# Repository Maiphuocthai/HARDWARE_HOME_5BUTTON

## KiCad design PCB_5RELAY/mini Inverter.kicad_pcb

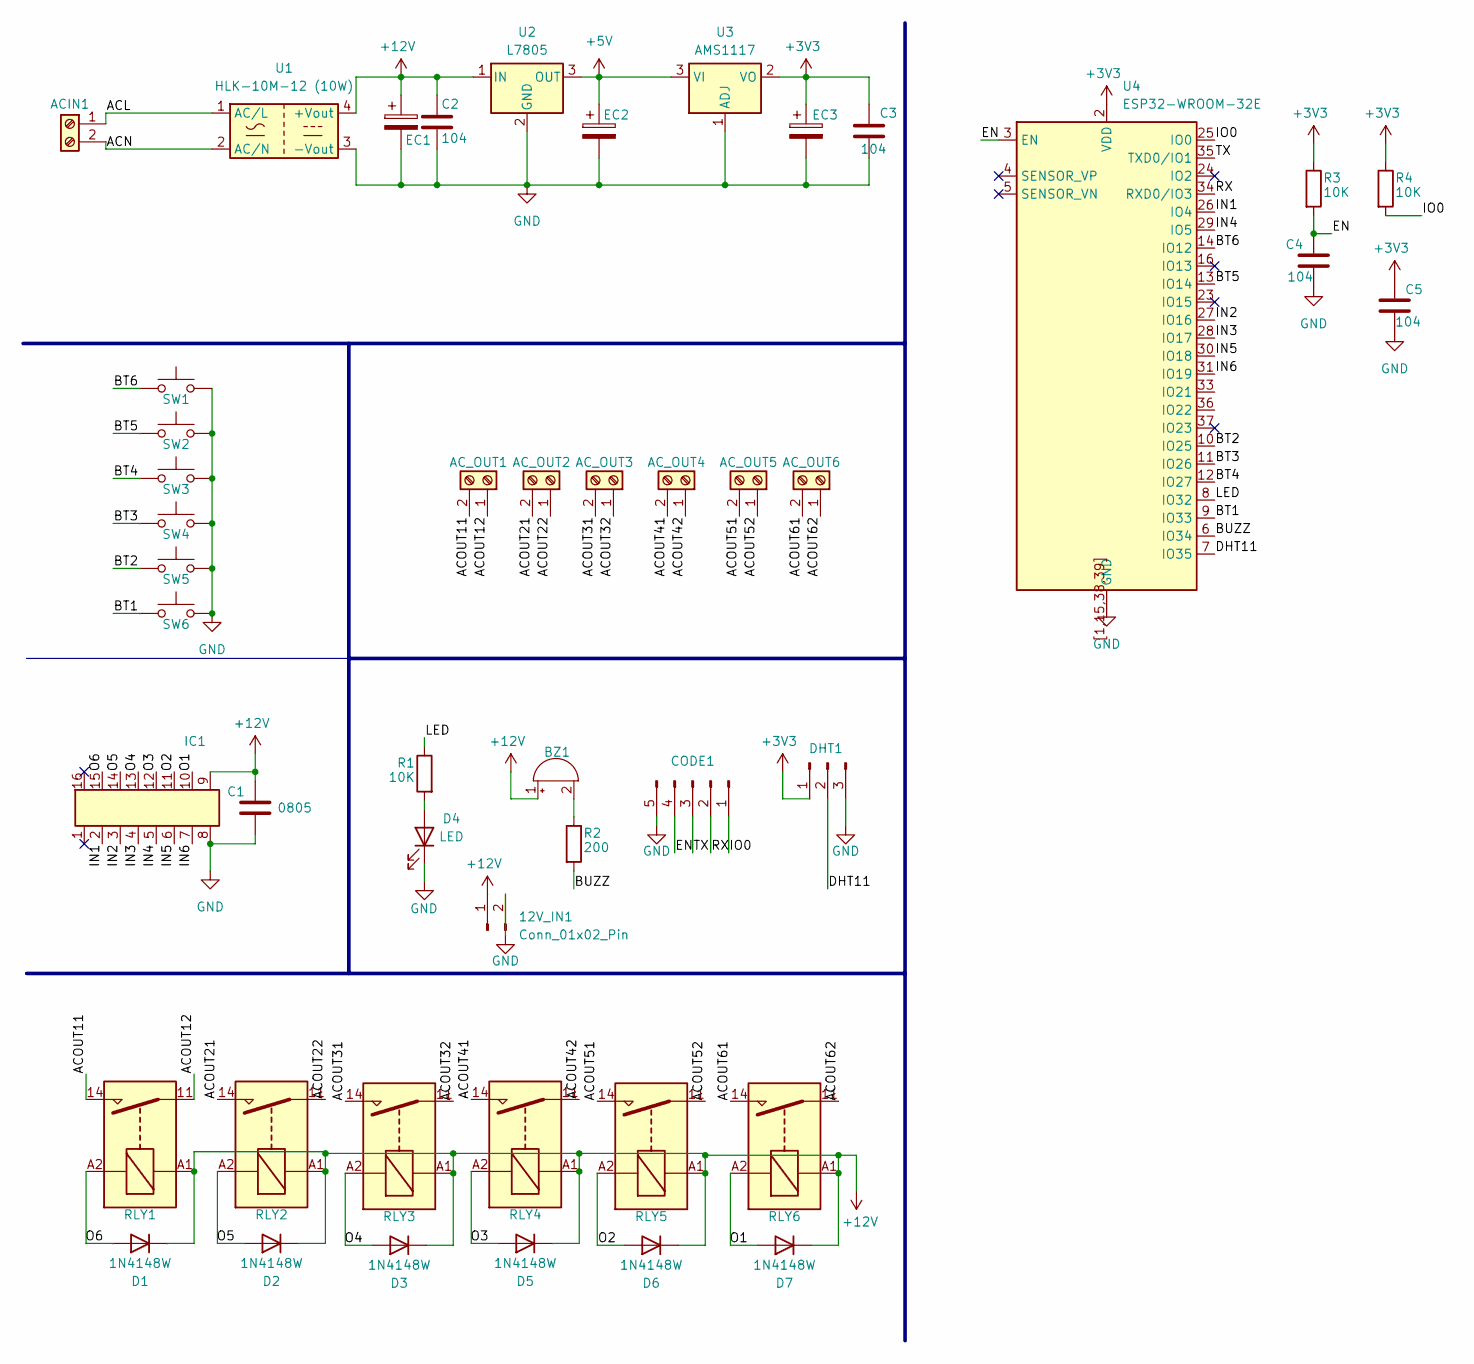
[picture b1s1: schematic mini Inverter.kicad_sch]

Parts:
12V_IN1: Conn_01x02_Pin; TerminalBlock_Xinya_XY308-2.54-2P_1x02_P2.54mm_Horizontal
ACIN1: Screw_Terminal_01x02; TerminalBlock_Phoenix_MKDS-1,5-2_1x02_P5.00mm_Horizontal
AC_OUT1, AC_OUT2, AC_OUT3, AC_OUT4, AC_OUT5, AC_OUT6: Screw_Terminal_01x02; TerminalBlock_Phoenix_MKDS-1,5-2_1x02_P5.00mm_Horizontal
BZ1: Buzzer; Indicator_PUI_AI-1440-TWT-24V-2-R
C1: 0805; R_0805_2012Metric
C2, C3, C4, C5: 104; R_0805_2012Metric
CODE1: Conn_01x05_Pin; PinHeader_1x05_P2.54mm_Vertical
D1, D2, D3, D5, D6, D7: 1N4148W; D_SOD-123
D4: LED; LED_0805_2012Metric
DHT1: Conn_01x03_Pin; DHT11
EC1: 220µF/25V; CP_Radial_D5.0mm_P2.50mm
EC2: 47µF; CP_Radial_D5.0mm_P2.50mm
EC3: 10µF; CP_Radial_D5.0mm_P2.50mm
IC1: ULN2003; JEITA_SOIC-16_3.9x9.9mm_P1.27mm
R1, R3, R4: 10K; R_0805_2012Metric
R2: 200; R_0805_2012Metric
RLY1, RLY2, RLY3, RLY4, RLY5, RLY6: GI-1A-12DH
SW1, SW2, SW3, SW4, SW5, SW6: Nút Nhấn 6x6mm Cao 5.5mm 2 Chân; Nút Nhấn 6x6mm Cao 5.5mm
U1: HLK-10M-12 (10W); Converter_ACDC_Hi-Link_HLK-PMxx
U2: L7805; TO-252-2
U3: AMS1117; SOT-223-3_TabPin2
U4: ESP32-WROOM-32E

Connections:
+3V3: C3.2, C5.1, DHT1.1, EC3.1, R3.1, R4.1, U3.2 (VO), U4.2 (VDD)
+5V: EC2.1, U2.3 (OUT), U3.3 (VI)
+12V: 12V_IN1.1, BZ1.1 (+), C1.1, C2.1, D1.1 (K), D2.1 (K), D3.1 (K), D5.1 (K), D6.1 (K), D7.1 (K), EC1.1, IC1.9, RLY1.A1, RLY2.A1, RLY3.A1, RLY4.A1, RLY5.A1, RLY6.A1, U1.4 (+Vout), U2.1 (IN)
/ACL: ACIN1.1, U1.1 (AC/L)
/ACN: ACIN1.2, U1.2 (AC/N)
/ACOUT11: AC_OUT1.2, RLY1.14
/ACOUT12: AC_OUT1.1, RLY1.11
/ACOUT21: AC_OUT2.2, RLY2.14
/ACOUT22: AC_OUT2.1, RLY2.11
/ACOUT31: AC_OUT3.2, RLY3.14
/ACOUT32: AC_OUT3.1, RLY3.11
/ACOUT41: AC_OUT4.2, RLY4.14
/ACOUT42: AC_OUT4.1, RLY4.11
/ACOUT51: AC_OUT5.2, RLY5.14
/ACOUT52: AC_OUT5.1, RLY5.11
/ACOUT61: AC_OUT6.2, RLY6.14
/ACOUT62: AC_OUT6.1, RLY6.11
/BT1: SW6.1, U4.9 (IO33)
/BT2: SW5.1, U4.10 (IO25)
/BT3: SW4.1, U4.11 (IO26)
/BT4: SW3.1, U4.12 (IO27)
/BT5: SW2.1, U4.13 (IO14)
/BT6: SW1.1, U4.14 (IO12)
/BUZZ: R2.2, U4.6 (IO34)
/DHT11: DHT1.2, U4.7 (IO35)
/EN: C4.1, CODE1.4, R3.2, U4.3 (EN)
/IN1: IC1.2, U4.26 (IO4)
/IN2: IC1.3, U4.27 (IO16)
/IN3: IC1.4, U4.28 (IO17)
/IN4: IC1.5, U4.29 (IO5)
/IN5: IC1.6, U4.30 (IO18)
/IN6: IC1.7, U4.31 (IO19)
/IO0: CODE1.1, R4.2, U4.25 (IO0)
/LED: R1.1, U4.8 (IO32)
/O1: D7.2 (A), IC1.10, RLY6.A2
/O2: D6.2 (A), IC1.11, RLY5.A2
/O3: D5.2 (A), IC1.12, RLY4.A2
/O4: D3.2 (A), IC1.13, RLY3.A2
/O5: D2.2 (A), IC1.14, RLY2.A2
/O6: D1.2 (A), IC1.15, RLY1.A2
/RX: CODE1.2, U4.34 (RXD0/IO3)
/TX: CODE1.3, U4.35 (TXD0/IO1)
GND: 12V_IN1.2, C1.2, C2.2, C3.1, C4.2, C5.2, CODE1.5, D4.1 (K), DHT1.3, EC1.2, EC2.2, EC3.2, IC1.8, SW1.2, SW2.2, SW3.2, SW4.2, SW5.2, SW6.2, U1.3 (-Vout), U2.2 (GND), U3.1 (ADJ), U4.1 (GND), U4.15 (GND), U4.38 (GND), U4.39 (GND), U4.[1,15,38,39] (GND)
unnamed: BZ1.2 (-), R2.1
unnamed: D4.2 (A), R1.2

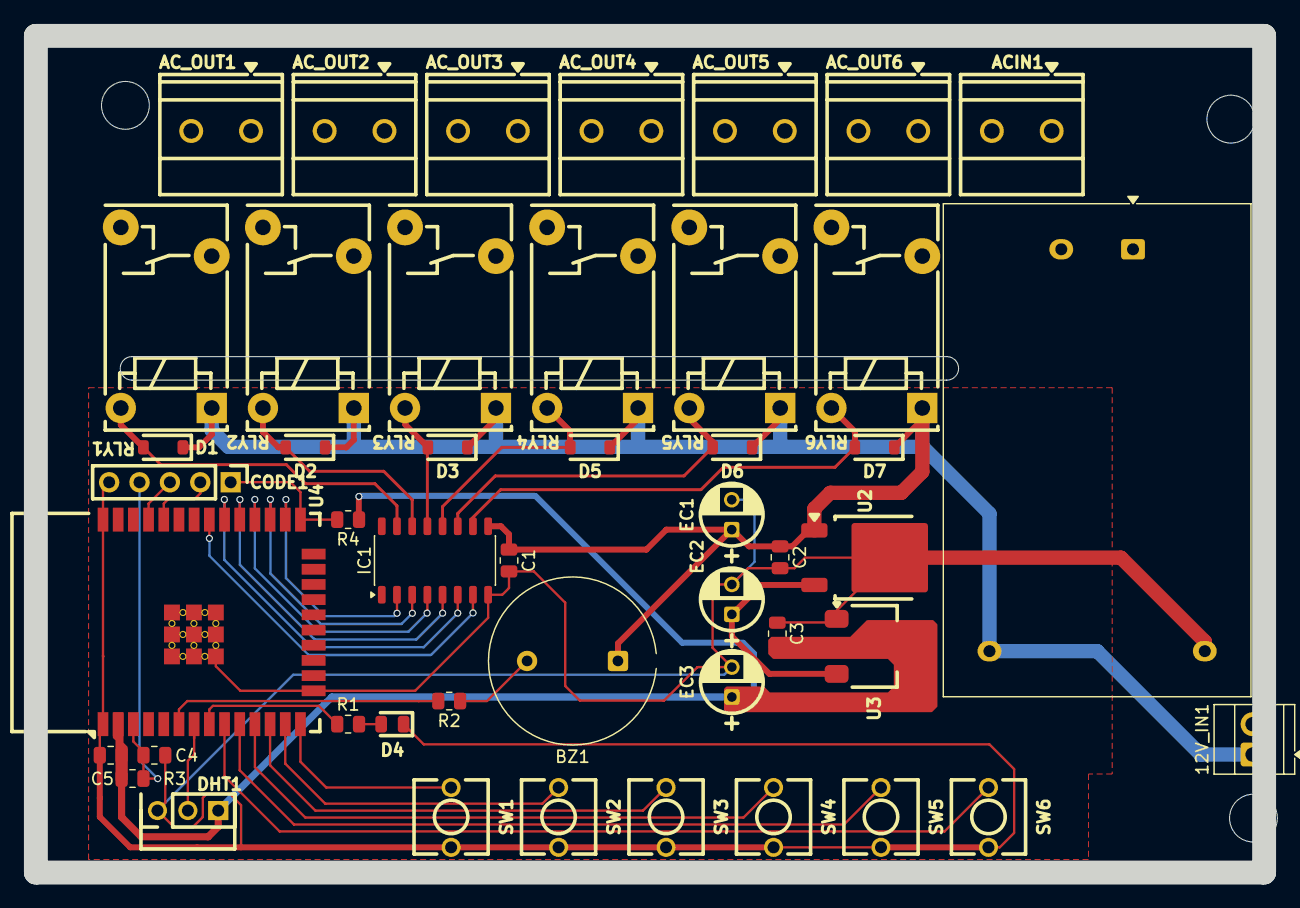
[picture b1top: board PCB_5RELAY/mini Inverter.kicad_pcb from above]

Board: 2 copper layers, 102.7 x 69.9 mm, 47 parts (0 on the bottom side), 45 nets.

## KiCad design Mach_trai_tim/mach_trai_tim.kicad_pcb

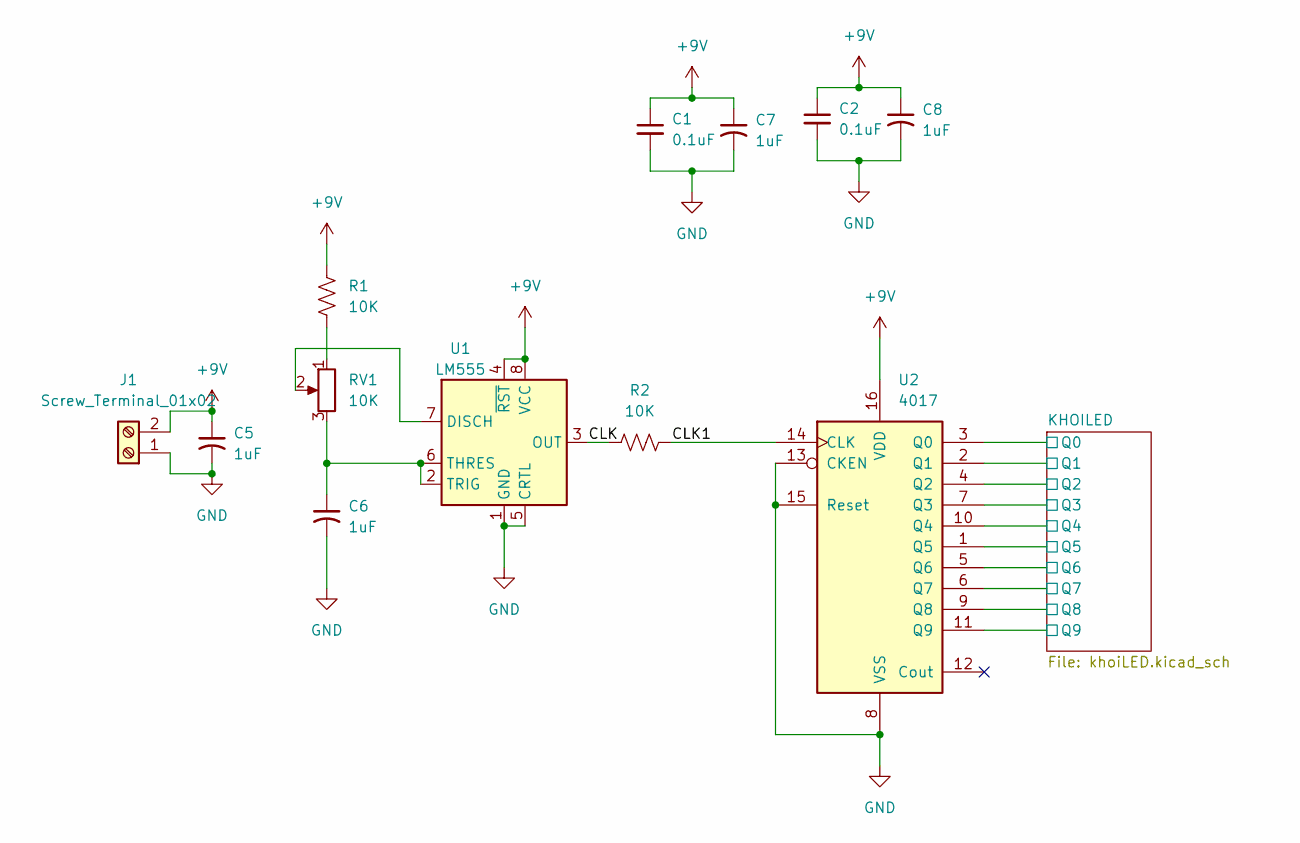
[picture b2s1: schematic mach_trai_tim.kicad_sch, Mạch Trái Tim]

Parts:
C1, C2: 0.1uF; Cap_104_THT
C5, C6, C7, C8: 1uF; CP_Radial_D5.0mm_P2.50mm
J1: Screw_Terminal_01x02; TerminalBlock_Phoenix_MKDS-1,5-2_1x02_P5.00mm_Horizontal
R1, R2: 10K; CFR25S
RV1: 10K; Potentiometer_Bourns_3296W_Vertical
U1: LM555; DIP-8_W7.62mm
U2: 4017; DIP-16_W7.62mm

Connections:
+9V: C1.1, C2.1, C5.1, C7.1, C8.1, J1.2, R1.2, U1.4 (~RST), U1.8 (VCC), U2.16 (VDD)
/CLK: R2.1, U1.3 (OUT)
/CLK1: R2.2, U2.14 (CLK)
/KHOILED/Q0: U2.3 (Q0); also elsewhere on the board
/KHOILED/Q1: U2.2 (Q1); also elsewhere on the board
/KHOILED/Q2: U2.4 (Q2); also elsewhere on the board
/KHOILED/Q3: U2.7 (Q3); also elsewhere on the board
/KHOILED/Q4: U2.10 (Q4); also elsewhere on the board
/KHOILED/Q5: U2.1 (Q5); also elsewhere on the board
/KHOILED/Q6: U2.5 (Q6); also elsewhere on the board
/KHOILED/Q7: U2.6 (Q7); also elsewhere on the board
/KHOILED/Q8: U2.9 (Q8); also elsewhere on the board
/KHOILED/Q9: U2.11 (Q9); also elsewhere on the board
GND: C1.2, C2.2, C5.2, C6.2, C7.2, C8.2, J1.1, U1.1 (GND), U1.5 (CRTL), U2.8 (VSS), U2.13 (CKEN), U2.15 (Reset); also elsewhere on the board
unnamed: R1.1, RV1.1
unnamed: RV1.2, U1.7 (DISCH)
unnamed: C6.1, RV1.3, U1.2 (TRIG), U1.6 (THRES)

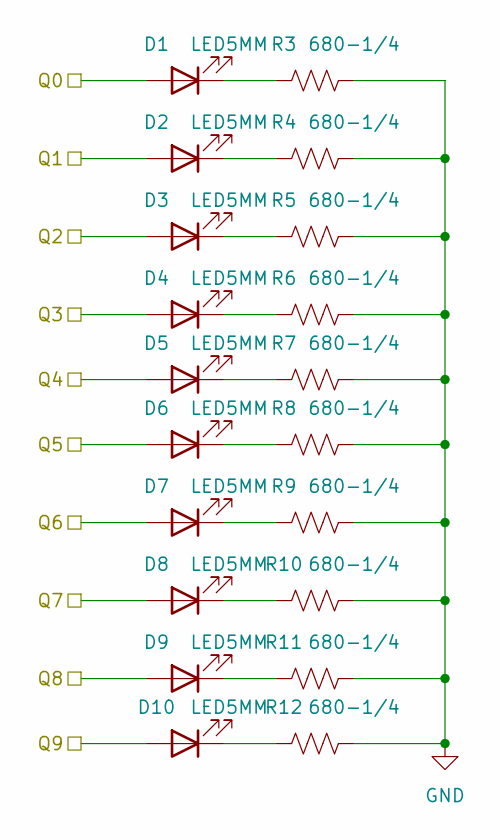
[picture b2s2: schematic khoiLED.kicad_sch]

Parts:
D1, D2, D3, D4, D5, D6, D7, D8, D9, D10: LED5MM; LED_D5.0mm
R3, R4, R5, R6, R7, R8, R9, R10, R11, R12: 680-1/4; CFR25S

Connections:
/KHOILED/Q0: D1.2 (A); also elsewhere on the board
/KHOILED/Q1: D2.2 (A); also elsewhere on the board
/KHOILED/Q2: D3.2 (A); also elsewhere on the board
/KHOILED/Q3: D4.2 (A); also elsewhere on the board
/KHOILED/Q4: D5.2 (A); also elsewhere on the board
/KHOILED/Q5: D6.2 (A); also elsewhere on the board
/KHOILED/Q6: D7.2 (A); also elsewhere on the board
/KHOILED/Q7: D8.2 (A); also elsewhere on the board
/KHOILED/Q8: D9.2 (A); also elsewhere on the board
/KHOILED/Q9: D10.2 (A); also elsewhere on the board
GND: R3.2, R4.2, R5.2, R6.2, R7.2, R8.2, R9.2, R10.2, R11.2, R12.2; also elsewhere on the board
unnamed: D1.1 (K), R3.1
unnamed: D2.1 (K), R4.1
unnamed: D3.1 (K), R5.1
unnamed: D4.1 (K), R6.1
unnamed: D5.1 (K), R7.1
unnamed: D6.1 (K), R8.1
unnamed: D7.1 (K), R9.1
unnamed: D8.1 (K), R10.1
unnamed: D9.1 (K), R11.1
unnamed: D10.1 (K), R12.1

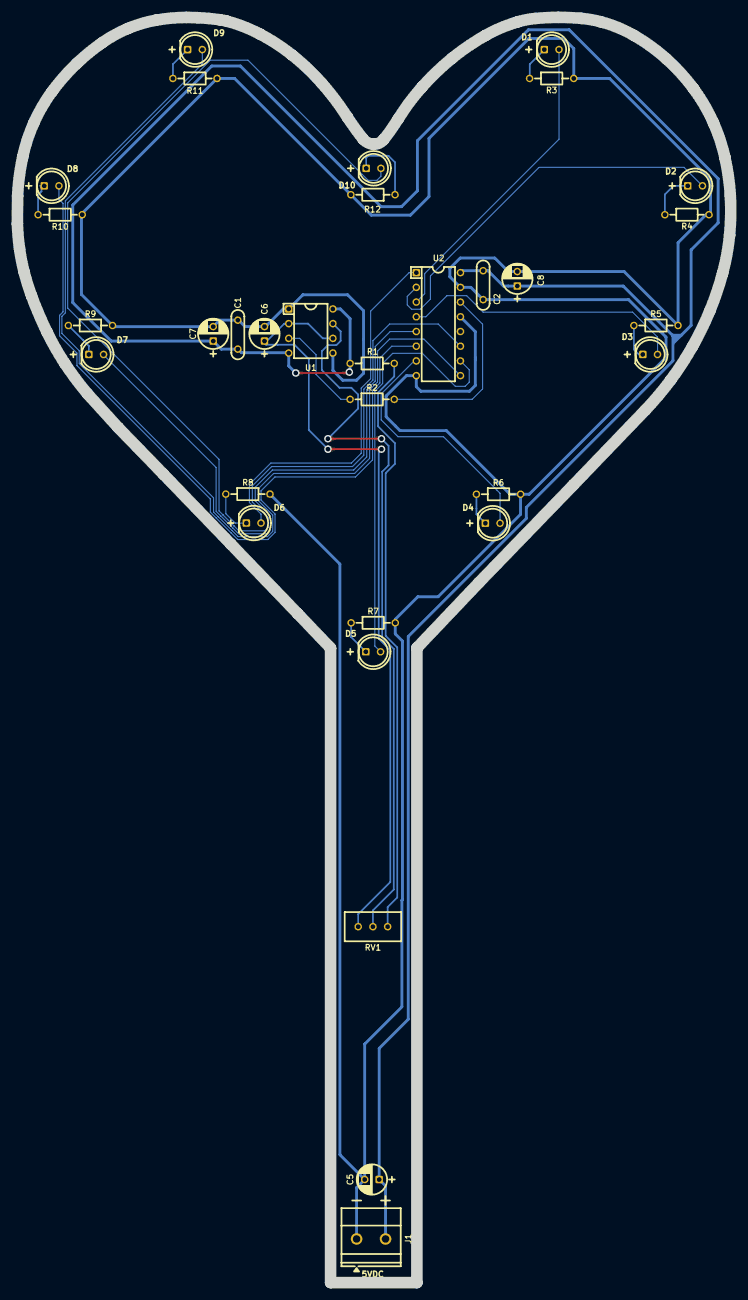
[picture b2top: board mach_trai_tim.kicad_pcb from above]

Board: 2 copper layers, 123.2 x 218.4 mm, 32 parts (0 on the bottom side), 27 nets.

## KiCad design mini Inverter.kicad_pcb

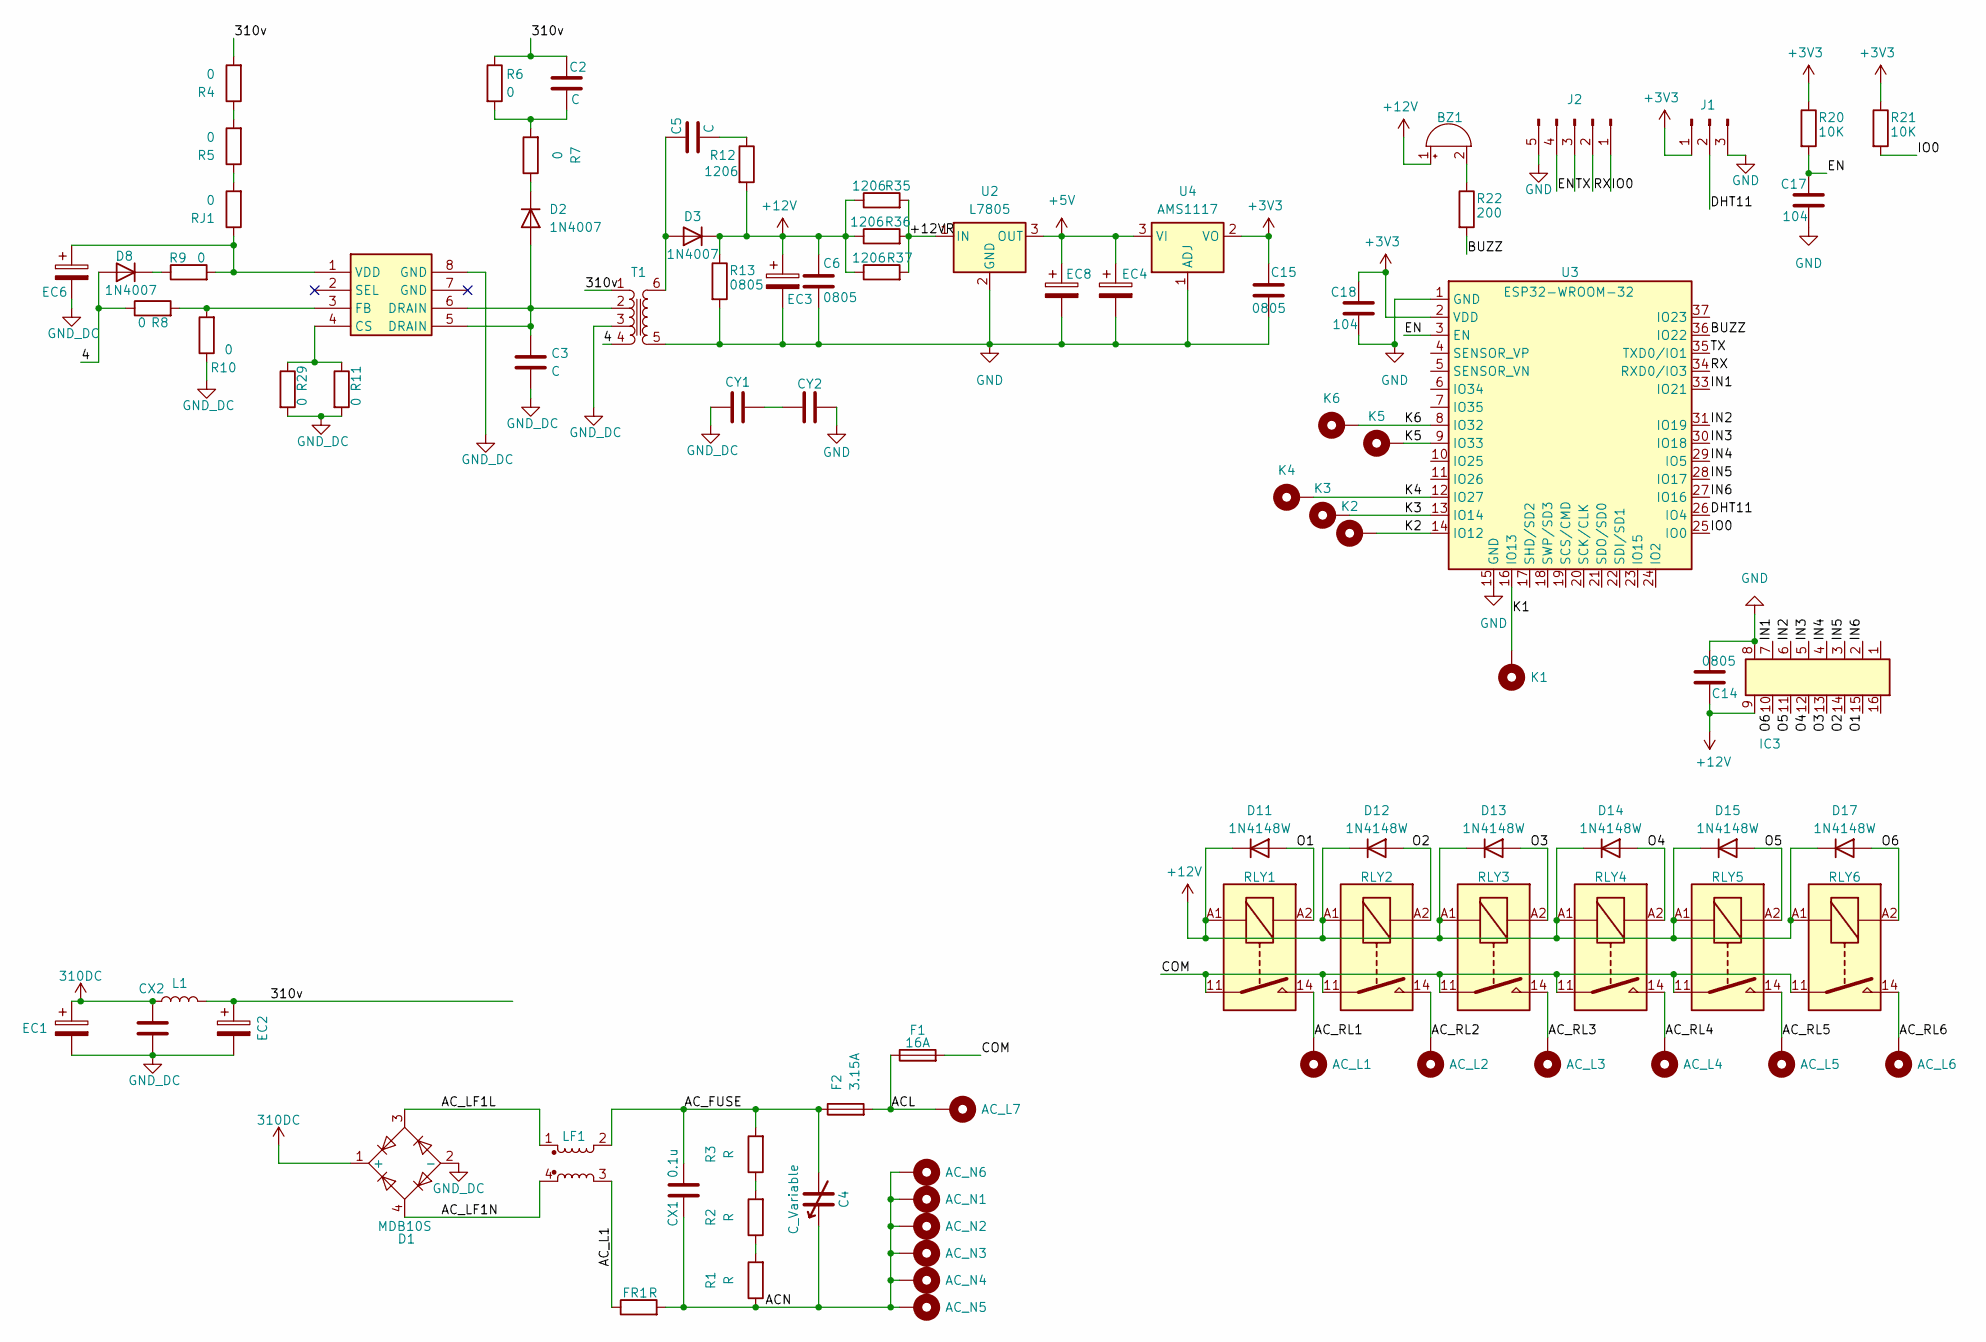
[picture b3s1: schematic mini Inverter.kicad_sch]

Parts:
AC_L1, AC_L2, AC_L3, AC_L4, AC_L5, AC_L6, AC_L7: MountingHole_Pad; PAD_AC
AC_N1, AC_N2, AC_N3, AC_N4, AC_N5, AC_N6: MountingHole_Pad; PAD_AC
BZ1: Buzzer; Indicator_PUI_AI-1440-TWT-24V-2-R
C2, C3, C5: C; C_Disc_D10.0mm_W2.5mm_P5.00mm
C4: C_Variable; RV_Disc_D12mm_W7.1mm_P7.5mm
C6, C14, C15: 0805; R_0805_2012Metric
C17, C18: 104; R_0805_2012Metric
CX1, CX2: 0.1u; C_Rect_L13.5mm_W5.0mm_P10.00mm_FKS3_FKP3_MKS4
CY1, CY2: C; TU CY
D1: MDB10S; TSSOP-4_4.4x5mm_P4mm
D2, D3, D8: 1N4007; D_SMA
D11, D12, D13, D14, D15, D17: 1N4148W; D_SOD-123
EC1, EC2, EC3: C_Polarized; CP_Radial_D10.0mm_P5.00mm
EC4, EC8: C_Polarized; CP_Radial_D6.3mm_P2.50mm
EC6: C_Polarized; CP_Radial_D5.0mm_P2.50mm
F1: 16A; FUSE 16A D28mm
F2: 3.15A; Fuse_Littelfuse_395Series
FR1: R; R_Axial_DIN0414_L11.9mm_D4.5mm_P5.08mm_Vertical
IC1: KP2122DP; DIP8 KP2122DP
IC3: ULN2003; JEITA_SOIC-16_3.9x9.9mm_P1.27mm
J1: Conn_01x03_Pin; PinHeader_1x03_P2.54mm_Vertical
J2: Conn_01x05_Pin; PinHeader_1x05_P2.54mm_Vertical
K1, K2, K3, K4, K5, K6: MountingHole_Pad; Touch_SF20
L1: L; L_Axial_L9.5mm_D4.0mm_P5.08mm_Vertical_Fastron_SMCC
LF1: L_Coupled_1243; UUAC
R1, R2, R3: R; R_1206_3216Metric
R4, R5, R6, R7, R9, R11, R29: 0; R_1206_3216Metric
R8, R10: 0; R_0805_2012Metric
R12, R35, R36, R37: 1206; R_1206_3216Metric
R13: 0805; R_0805_2012Metric
R20, R21: 10K; R_0805_2012Metric
R22: 200; R_0805_2012Metric
RJ1: 0; R_1206_3216Metric
RLY1, RLY2, RLY3, RLY4, RLY5, RLY6: GI-1A-12DH
T1: Bien_ap_KP2122
U2: L7805; TO-252-2
U3: ESP32-WROOM-32
U4: AMS1117; SOT-223-3_TabPin2

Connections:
310DC: CX2.1, D1.1 (+), EC1.1, L1.1
+3V3: C15.2, C18.1, J1.1, R20.1, R21.1, U3.2 (VDD), U4.2 (VO)
+5V: EC4.1, EC8.1, U2.3 (OUT), U4.3 (VI)
+12V: BZ1.1 (+), C6.1, C14.1, D3.1 (K), D11.1 (K), D12.1 (K), D13.1 (K), D14.1 (K), D15.1 (K), D17.1 (K), EC3.1, IC3.9, R12.2, R13.1, R35.1, R36.1, R37.1, RLY1.A1, RLY2.A1, RLY3.A1, RLY4.A1, RLY5.A1, RLY6.A1
/4: D8.2 (A), R8.1, T1.4
/310v: C2.2, EC2.1, L1.2, R4.2, R6.1, T1.1
/+12VR: R35.2, R36.2, R37.2, U2.1 (IN)
/ACL: AC_L7.1, F1.1, F2.2
/ACN: AC_N1.1, AC_N2.1, AC_N3.1, AC_N4.1, AC_N5.1, AC_N6.1, C4.1, CX1.1, FR1.2, R1.1
/AC_FUSE: C4.2, CX1.2, F2.1, LF1.2, R3.2
/AC_L1: FR1.1, LF1.3
/AC_LF1L: D1.3, LF1.1
/AC_LF1N: D1.4, LF1.4
/AC_RL1: AC_L1.1, RLY1.14
/AC_RL2: AC_L2.1, RLY2.14
/AC_RL3: AC_L3.1, RLY3.14
/AC_RL4: AC_L4.1, RLY4.14
/AC_RL5: AC_L5.1, RLY5.14
/AC_RL6: AC_L6.1, RLY6.14
/BUZZ: R22.2, U3.36 (IO22)
/COM: F1.2, RLY1.11, RLY2.11, RLY3.11, RLY4.11, RLY5.11, RLY6.11
/DHT11: J1.2, U3.26 (IO4)
/EN: C17.1, J2.4, R20.2, U3.3 (EN)
/IN1: IC3.7, U3.33 (IO21)
/IN2: IC3.6, U3.31 (IO19)
/IN3: IC3.5, U3.30 (IO18)
/IN4: IC3.4, U3.29 (IO5)
/IN5: IC3.3, U3.28 (IO17)
/IN6: IC3.2, U3.27 (IO16)
/IO0: J2.1, R21.2, U3.25 (IO0)
/K1: K1.1, U3.16 (IO13)
/K2: K2.1, U3.14 (IO12)
/K3: K3.1, U3.13 (IO14)
/K4: K4.1, U3.12 (IO27)
/K5: K5.1, U3.9 (IO33)
/K6: K6.1, U3.8 (IO32)
/O1: D11.2 (A), IC3.15, RLY1.A2
/O2: D12.2 (A), IC3.14, RLY2.A2
/O3: D13.2 (A), IC3.13, RLY3.A2
/O4: D14.2 (A), IC3.12, RLY4.A2
/O5: D15.2 (A), IC3.11, RLY5.A2
/O6: D17.2 (A), IC3.10, RLY6.A2
/RX: J2.2, U3.34 (RXD0/IO3)
/TX: J2.3, U3.35 (TXD0/IO1)
GND: C6.2, C14.2, C15.1, C17.2, C18.2, CY2.2, EC3.2, EC4.2, EC8.2, IC3.8, J1.3, J2.5, R13.2, T1.5, U2.2 (GND), U3.1 (GND), U3.15 (GND), U4.1 (ADJ)
GND_DC: C3.1, CX2.2, CY1.1, D1.2 (-), EC1.2, EC2.2, EC6.2, IC1.8 (GND), R10.1, R11.2, R29.2, T1.3
unnamed: BZ1.2 (-), R22.1
unnamed: C2.1, R6.2, R7.2
unnamed: C5.1, R12.1
unnamed: CY1.2, CY2.1
unnamed: C3.2, D2.2 (A), IC1.5 (DRAIN), IC1.6 (DRAIN), T1.2
unnamed: D2.1 (K), R7.1
unnamed: C5.2, D3.2 (A), T1.6
unnamed: D8.1 (K), R9.1
unnamed: IC1.4 (CS), R11.1, R29.1
unnamed: IC1.3 (FB), R8.2, R10.2
unnamed: EC6.1, IC1.1 (VDD), R9.2, RJ1.1
unnamed: R1.2, R2.1
unnamed: R2.2, R3.1
unnamed: R4.1, R5.2
unnamed: R5.1, RJ1.2

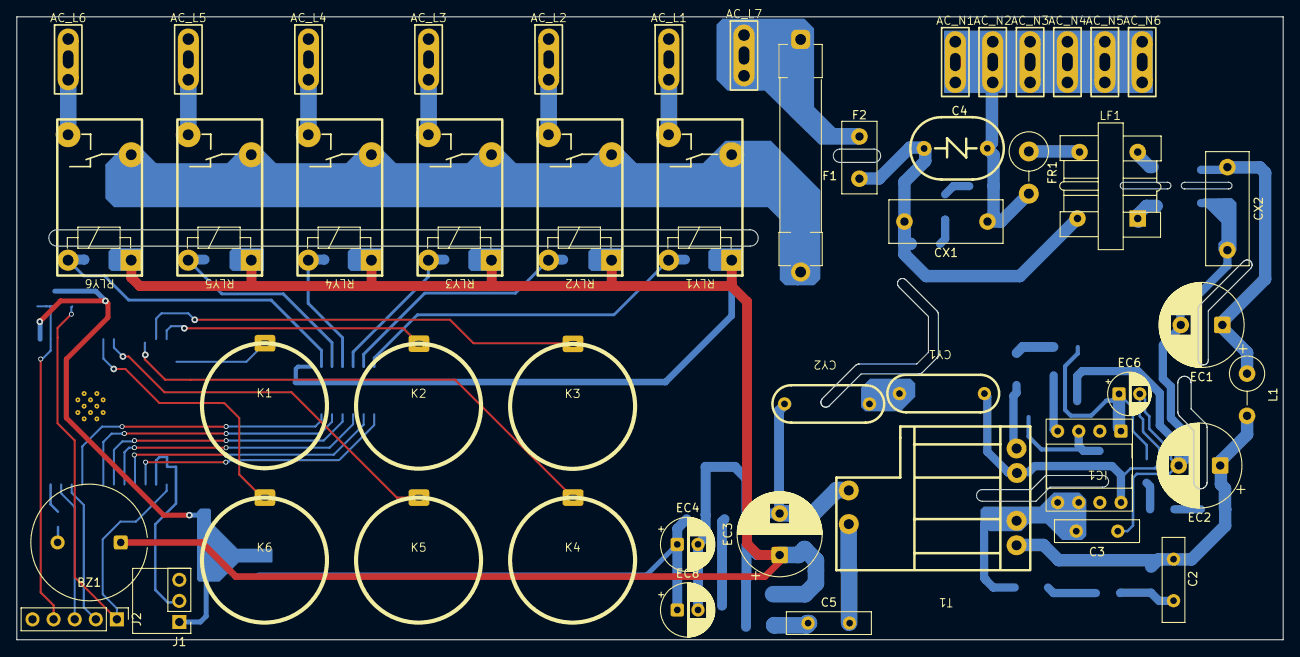
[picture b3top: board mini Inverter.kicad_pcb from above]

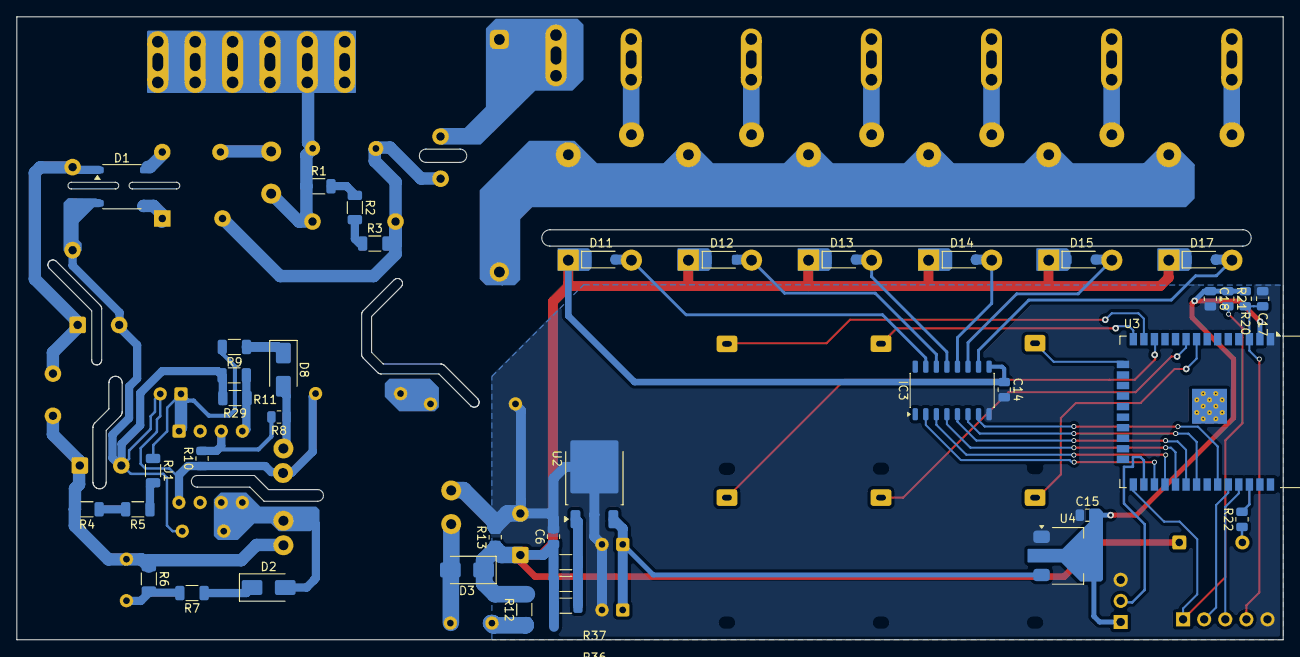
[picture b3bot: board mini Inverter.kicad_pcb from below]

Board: 2 copper layers, 152.5 x 75.0 mm, 89 parts (40 on the bottom side), 61 nets.
